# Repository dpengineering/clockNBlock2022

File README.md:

# ToDo List
[Google Doc Link](https://docs.google.com/document/d/1s_93HzQu_74fJWDLWwISt_NYs3OvQ41pf5nRqQ8sUA4/edit?usp=sharing).  
Please request access if you would like to change the doc or check things off.  

# ClockNBlock 2022 Version
Written by `@ArnavVWadhwa` and `@bvesper15` this is the new version of the clockNBlock project with the "shiny new delta arm." The major changes this year was to the circuit boards used. We added `@Stan-Reifel's` new DPi Circuit boards and redid the wiring. 
  
The code is also completely brand new and this is the third version of the code I have written. I hope it holds up to a good standard.

For any questions with the project feel free to reach out me.  
Arnav Wadhwa:  
(805) 570-5030.   
arnav.v.wadhwa@gmail.com

Note: When you contact me please let me know who you are and that this is for the clock and block so I don't accidently ignore you.

Here is the fun story for the project.
# It Clocks! It Blocks! New and improved only at Faker Maire!

# A Tale of Two Arms

This is the repository for the redesigned ClockNBlocks. The ClockNBlocks is a project in which a robotic arm stacks block towers, and sweeping clock hands susequently knock over the towers.

The project was first developed in the 2016-17 school year, employing a gantry-style serial manipulator arm. It wasn't fast; it wasn't elegant, but in ran like a beauty. The code for this version of the project was perfected by `@jproney` himself in the fall of 2017, and can be found here: https://github.com/dpengineering/ClockNBlockHW

After `@jproney's` labors to perfect the CNB, the original project was torn apart, and the slow, sturdy gantry arm replaced with a shiny new Delta Robot. What is a Delta Robot you ask? Luckily for you, `@jproney` made https://github.com/dpengineering/DeltaArm to answer this age old question. The DeltaArm repository contains the Inverse Kinematic and Forward Kinematic equations for controlling the new Delta Arm.

But that's not where the story ends. The original ClockNBlock was powered by an artificial brain known as the R-dwino (sometimes stylized _Arduino_). However, the new arm was to be controlled by a Pi of Raspberry and it's trusty companion, the Engine of Slush. Therefore, it became necessary for the Arduinos controlling the project's pneumatic actuators to communicate with the Rasperry Pi. To accomplish this task, `@jproney` created https://github.com/dpengineering/PythonManager by standing of the shoulders of `@jmgrosen`, the hero who first brought peace to Mechatronica. Unfortunately,
PythonManager was developed quite hastily, and is currently rather messy and confusing. 

And now that brings us here. The repository you are viewing combines the DeltaArm, PythonManager, and old ClockNBlockHW repositiories to create ClockNBlockPi. In its current state, the ClockNBlock runs, but not well. The arm control software (forward/inverse kinematics) works quite well, but for one reason or another the arm struggles to maintain the sub-inch precision required to pick up blocks consistently. This is likely due to backlash in the arm transmissions, slippage in shaft couplers, and inconsistencies in the homing of the arm.

Now you come into the story, young squire. Your task is to tame the Arm of Delta, build the Block Towers high once more, and bring the ClockNBlock back to its golden age. Godspeed.

Sincerely,
James "Petey/Stagflation/jproney" Roney

P.S. I did most (all) of these - Arnav

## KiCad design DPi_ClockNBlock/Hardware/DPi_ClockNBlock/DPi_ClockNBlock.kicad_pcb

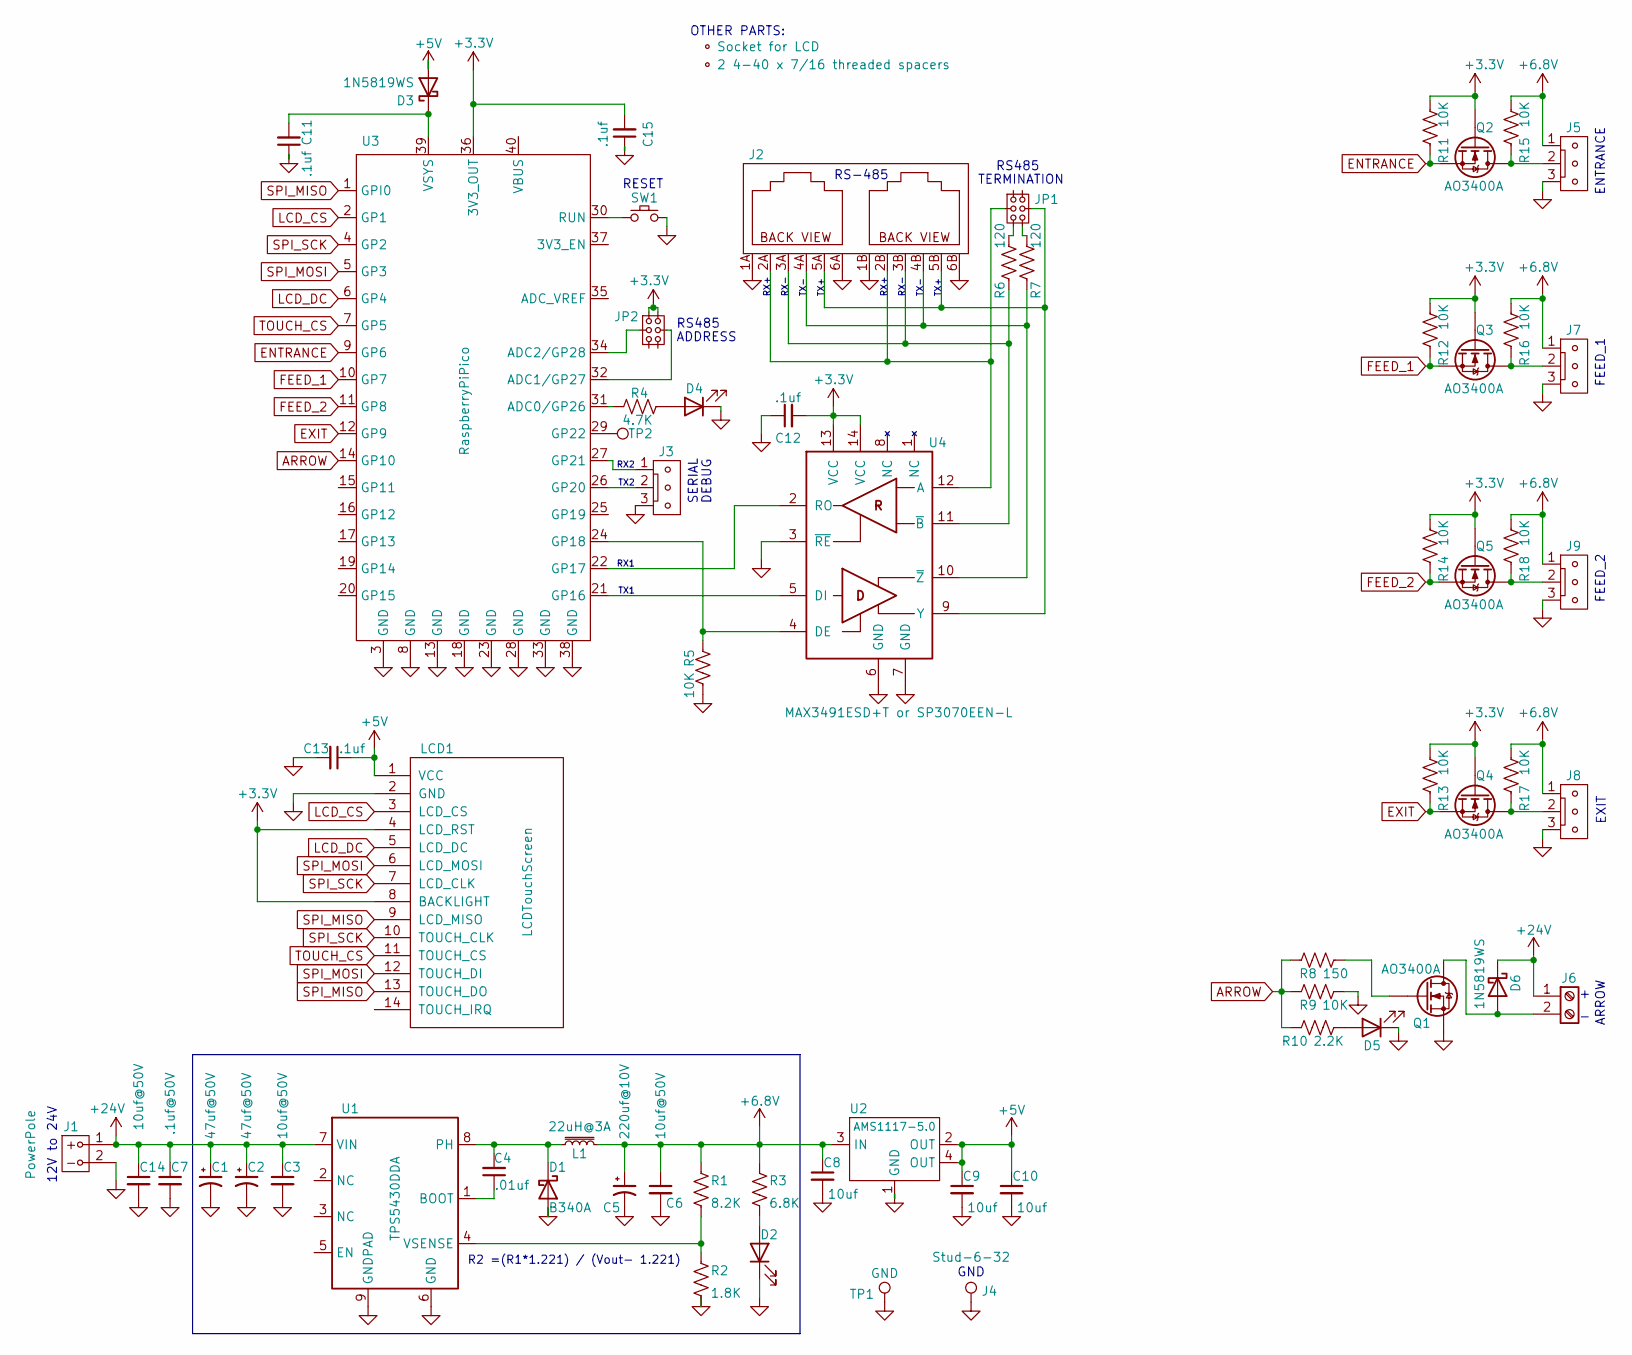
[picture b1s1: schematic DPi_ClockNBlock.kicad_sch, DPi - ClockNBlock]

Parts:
AP1: Socket for LCD
AP2: 2 4-40 x 7/16 threaded spacers
C1, C2: 47uf@50V; CP_Elec_6.3x7.7
C3, C6, C14: 10uf@50V; C_0805_2012Metric
C4: .01uf; C_0805_2012Metric
C5: 220uf@10V; CP_Elec_6.3x7.7
C7: .1uf@50V; C_0805_2012Metric
C8, C9, C10: 10uf; C_0805_2012Metric
C11, C12, C13, C15: .1uf; C_0805_2012Metric
D1: B340A; D_SMA
D2, D4, D5: RED LED; LED_0805_2012Metric
D3, D6: 1N5819WS; D_SOD-323
J1: PowerPole2
J2: 6P6C_Modular_Dual
J3, J5, J7, J8, J9: Molex-Vert-3-L; Molex-Vert-3
J4: Stud-6-32; ThreadedStud_6-32-375
J6: ScrewTerminal3.5MM-2
JP1, JP2: Jumper3x2
L1: 22uH@3A; Inductor_6.6x7.1_H3
LCD1: LCDTouchScreen
Q1, Q2, Q3, Q4, Q5: AO3400A; SOT-23
R1: 8.2K; R_0805_2012Metric
R2: 1.8K; R_0805_2012Metric
R3: 6.8K; R_0805_2012Metric
R4: 4.7K; R_0805_2012Metric
R5, R9, R11, R12, R13, R14, R15, R16, R17, R18: 10K; R_0805_2012Metric
R6, R7: 120; R_0805_2012Metric
R8: 150; R_0805_2012Metric
R10: 2.2K; R_0805_2012Metric
SW1: PushButton_C318884
TP1: GND; TestPoint
TP2: GP22; TestPoint
U1: TPS5430DDA; TI_SO-PowerPAD-8_ThermalVias
U2: AMS1117-5.0; SOT-223
U3: RaspberryPiPico
U4: MAX3491ESD+T or SP3070EEN-L; SOIC-14_3.9x8.7mm_P1.27mm

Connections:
+3V3: C12.2, C15.2, JP2.1, JP2.2, LCD1.4 (LCD_RST), LCD1.8 (BACKLIGHT), Q2.1 (G), Q3.1 (G), Q4.1 (G), Q5.1 (G), R11.2, R12.2, R13.2, R14.2, U3.36 (3V3_OUT), U4.13 (VCC), U4.14 (VCC)
+5V: C9.1, C10.1, C13.1, D3.2 (A), LCD1.1 (VCC), U2.2 (OUT), U2.4 (OUT)
+6.8V: C5.1, C6.1, C8.1, J5.1, J7.1, J8.1, J9.1, L1.2, R1.1, R3.1, R15.2, R16.2, R17.2, R18.2, U2.3 (IN)
+24V: C1.1, C2.1, C3.1, C7.1, C14.1, D6.1 (K), J1.1, J6.1, U1.7 (VIN)
ARROW: R8.1, R9.1, R10.1, U3.14 (GP10)
ENTRANCE: Q2.2 (S), R11.1, U3.9 (GP6)
EXIT: Q4.2 (S), R13.1, U3.12 (GP9)
FEED_1: Q3.2 (S), R12.1, U3.10 (GP7)
FEED_2: Q5.2 (S), R14.1, U3.11 (GP8)
GND: C1.2, C2.2, C3.2, C5.2, C6.2, C7.2, C8.2, C9.2, C10.2, C11.1, C12.1, C13.2, C14.2, C15.1, D1.2 (A), D2.1 (K), D4.1 (K), D5.1 (K), J1.2, J2.1A, J2.1B, J2.6A, J2.6B, J3.3, J4.1, J5.3, J7.3, J8.3, J9.3, LCD1.2 (GND), Q1.2 (S), R2.2, R5.2, R9.2, SW1.2, TP1.1, U1.6 (GND), U1.9 (GNDPAD), U2.1 (GND), U3.3 (GND), U3.8 (GND), U3.13 (GND), U3.18 (GND), U3.23 (GND), U3.28 (GND), U3.33 (GND), U3.38 (GND), U4.3 (~RE), U4.6 (GND), U4.7 (GND)
LCD_CS: LCD1.3 (LCD_CS), U3.2 (GP1)
LCD_DC: LCD1.5 (LCD_DC), U3.6 (GP4)
unnamed: C4.1, U1.1 (BOOT)
unnamed: C4.2, D1.1 (K), L1.1, U1.8 (PH)
unnamed: C11.2, D3.1 (K), U3.39 (VSYS)
unnamed: D2.2 (A), R3.2
unnamed: D4.2 (A), R4.2
unnamed: D5.2 (A), R10.2
unnamed: D6.2 (A), J6.2, Q1.3 (D)
unnamed: J2.2A, J2.2B, JP1.3, U4.12 (A)
unnamed: J2.3A, J2.3B, R6.1, U4.11 (~B)
unnamed: J2.4A, J2.4B, R7.1, U4.10 (~Z)
unnamed: J2.5A, J2.5B, JP1.4, U4.9 (Y)
unnamed: J3.1, U3.27 (GP21)
unnamed: J3.2, U3.26 (GP20)
unnamed: J5.2, Q2.3 (D), R15.1
unnamed: J7.2, Q3.3 (D), R16.1
unnamed: J8.2, Q4.3 (D), R17.1
unnamed: J9.2, Q5.3 (D), R18.1
unnamed: JP1.5, R6.2
unnamed: JP1.6, R7.2
unnamed: JP2.3, U3.34 (ADC2/GP28)
unnamed: JP2.4, U3.32 (ADC1/GP27)
unnamed: Q1.1 (G), R8.2
unnamed: R1.2, R2.1, U1.4 (VSENSE)
unnamed: R4.1, U3.31 (ADC0/GP26)
unnamed: R5.1, U3.24 (GP18), U4.4 (DE)
unnamed: SW1.1, U3.30 (RUN)
unnamed: TP2.1, U3.29 (GP22)
unnamed: U3.21 (GP16), U4.5 (DI)
unnamed: U3.22 (GP17), U4.2 (RO)
SPI_MISO: LCD1.9 (LCD_MISO), LCD1.13 (TOUCH_DO), U3.1 (GPI0)
SPI_MOSI: LCD1.6 (LCD_MOSI), LCD1.12 (TOUCH_DI), U3.5 (GP3)
SPI_SCK: LCD1.7 (LCD_CLK), LCD1.10 (TOUCH_CLK), U3.4 (GP2)
TOUCH_CS: LCD1.11 (TOUCH_CS), U3.7 (GP5)

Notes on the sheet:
SERIAL
TERMINATION
TX2
RX2
RX-
RESET
EXIT
TX+
RS-485
RX1
GND
ENTRANCE
12V to 24V
TX-
DEBUG
RS485
OTHER PARTS:
FEED_1
RX+
TX1
R2 =(R1*1.221) / (Vout- 1.221)
ADDRESS
ARROW
FEED_2

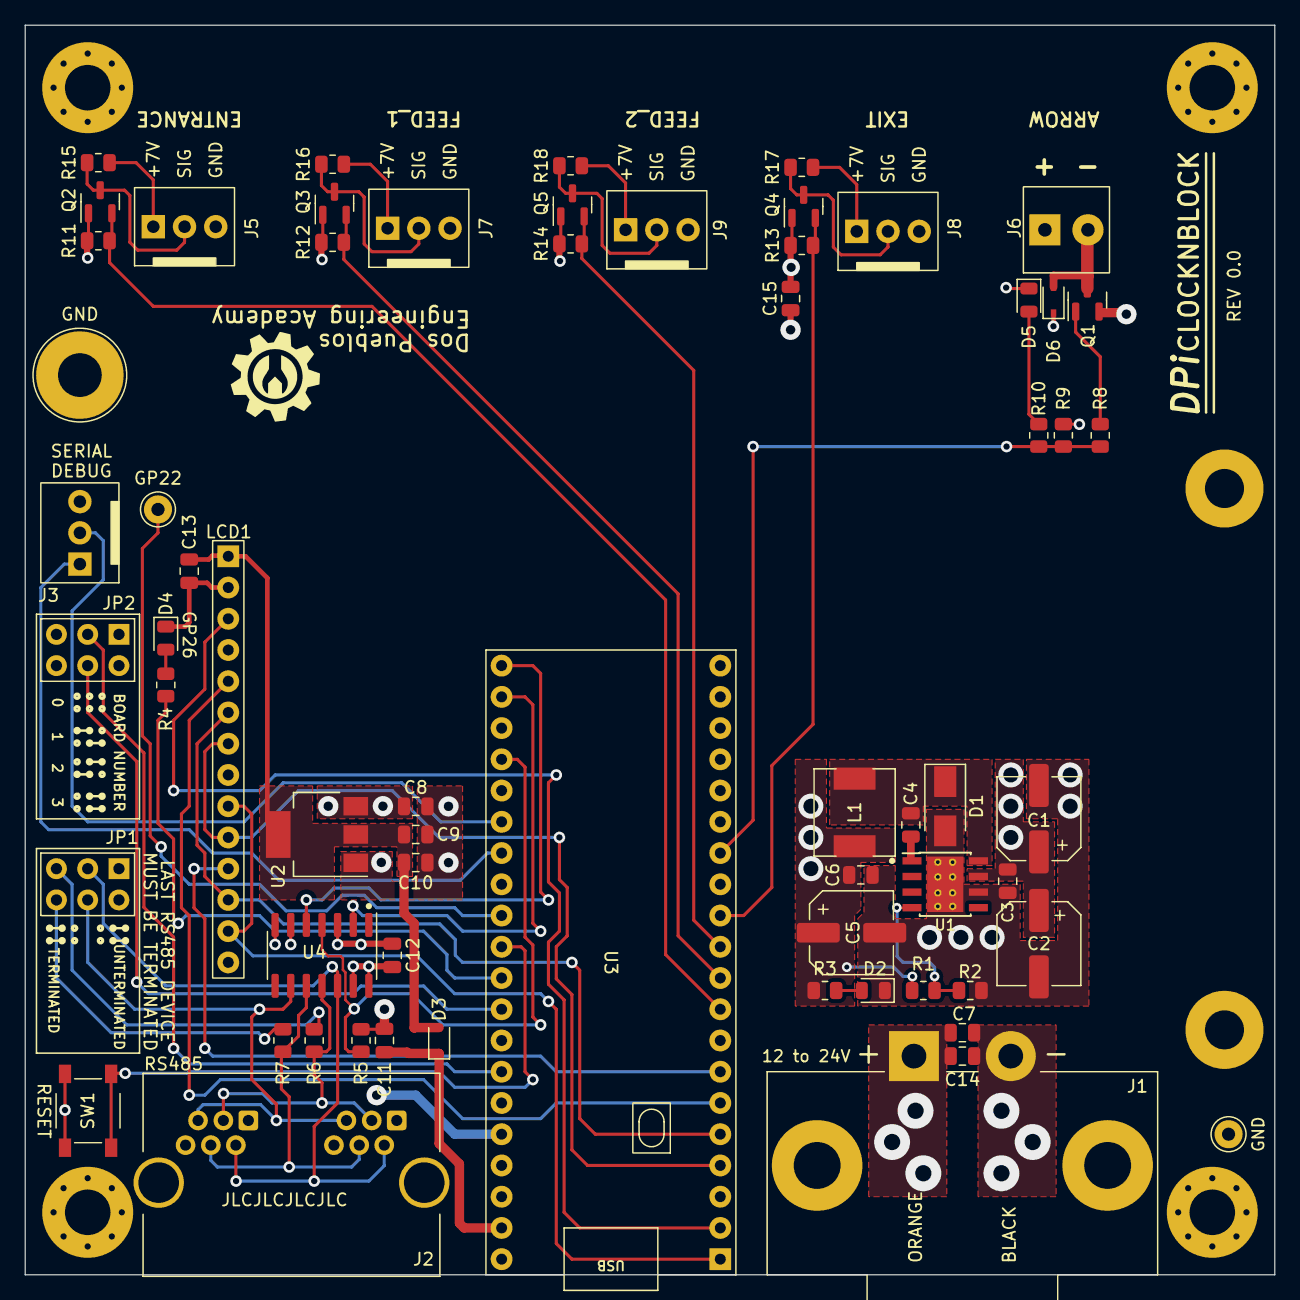
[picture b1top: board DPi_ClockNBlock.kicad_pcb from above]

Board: 4 copper layers, 101.6 x 101.6 mm, 64 parts (0 on the bottom side), 45 nets.

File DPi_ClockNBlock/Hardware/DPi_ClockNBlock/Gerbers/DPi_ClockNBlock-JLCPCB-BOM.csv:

Comment,Designator,Footprint,LCSC
47uf@50V,"C1,C2",Capacitor_SMD:CP_Elec_6.3x7.7,C401824
.1uf,"C11,C12,C13,C15",Capacitor_SMD:C_0805_2012Metric,C49678
10uf@50V,"C3,C6,C14",Capacitor_SMD:C_0805_2012Metric,C440198
.01uf,C4,Capacitor_SMD:C_0805_2012Metric,C1710
220uf@10V,C5,Capacitor_SMD:CP_Elec_6.3x7.7,C134763
.1uf@50V,C7,Capacitor_SMD:C_0805_2012Metric,C49678
10uf,"C8,C9,C10",Capacitor_SMD:C_0805_2012Metric,C440198
B340A,D1,Diode_SMD:D_SMA,C64982
RED LED,"D2,D4,D5",LED_SMD:LED_0805_2012Metric,C2297
1N5819WS,"D3,D6",Diode_SMD:D_SOD-323,C191023
22uH@3A,L1,@CustomFootprints_Discrete:Inductor_6.6x7.1_H3,C497873
AO3400A,"Q1,Q2,Q3,Q4,Q5",Package_TO_SOT_SMD:SOT-23,C20917
8.2K,R1,Resistor_SMD:R_0805_2012Metric,C17828
2.2K,R10,Resistor_SMD:R_0805_2012Metric,C17520
1.8K,R2,Resistor_SMD:R_0805_2012Metric,C17398
6.8K,R3,Resistor_SMD:R_0805_2012Metric,C17772
4.7K,R4,Resistor_SMD:R_0805_2012Metric,C17673
10K,"R5,R9,R11,R12,R13,R14,R15,R16,R17,R18",Resistor_SMD:R_0805_2012Metric,C17414
120,"R6,R7",Resistor_SMD:R_0805_2012Metric,C17437
150,R8,Resistor_SMD:R_0805_2012Metric,C17471
PushButton_C318884,SW1,@CustomFootprints_Discrete:PushButton_C318884,C318884
TPS5430DDA,U1,Package_SO:TI_SO-PowerPAD-8_ThermalVias,C9864
AMS1117-5.0,U2,Package_TO_SOT_SMD:SOT-223,C6187
MAX3491ESD+T or SP3070EEN-L,U4,Package_SO:SOIC-14_3.9x8.7mm_P1.27mm,C150204

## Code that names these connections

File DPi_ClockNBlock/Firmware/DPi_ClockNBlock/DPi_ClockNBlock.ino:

//      ******************************************************************
//      *                                                                *
//      *                       DPi - ClockNBlock                        *
//      *                                                                *
//      *            Arnav Wadhwa                  11/25/2022            *
//      *                                                                *
//      ******************************************************************

#include <Arduino.h>
#include "Constants.h"
#include "RS485Slave.h"
#include "CmdProcessor.h"

//
// variables global to this file
//
int boardNumber;


// ---------------------------------------------------------------------------------
//                              Hardware and software setup
// ---------------------------------------------------------------------------------

//
// top level setup function
//
void setup()
{
    debug_Initialize();
    debug("Starting...");

    //
    // initialize the all the inputs
    //
    pinMode(ENTRANCE_PIN, INPUT);
    pinMode(FEED_1_PIN, INPUT);
    pinMode(FEED_2_PIN, INPUT);
    pinMode(EXIT_PIN, INPUT);
 
    pinMode(ARROW_PIN, OUTPUT);
    digitalWrite(ARROW_PIN, LOW);

    //
    // determine the board number (as configured by jumps) for this board (0 - 3)
    //
    pinMode(RS486_ADDRESS_0_PIN, INPUT_PULLDOWN);
    pinMode(RS486_ADDRESS_1_PIN, INPUT_PULLDOWN);
    boardNumber = 0;
    if (digitalRead(RS486_ADDRESS_0_PIN)) boardNumber += 1;
    if (digitalRead(RS486_ADDRESS_1_PIN)) boardNumber += 2;

    //
    // initialize other IO lines
    //
    pinMode(LED_PIN, OUTPUT);
    digitalWrite(LED_PIN, LOW);
    pinMode(TEST_PIN, OUTPUT);

    //
    // initialize the software modules
    //
    cmdProcessor_Initialize(boardNumber);
    heartbeatLED_Initialize();
}


// ---------------------------------------------------------------------------------
//                      The Main Loop and Top Level Functions
// ---------------------------------------------------------------------------------


//
// main loop - execute commands from the Master
//
void loop()
{
    while(true)
    {
        //
        // check for and process commands from the Master
        //
        cmdProcessor_Execute();

        //
        // update the "heartbeat" LED
        //
        heartbeatLED_Update();
    }
}



// ---------------------------------------------------------------------------------
//                      Functions for the Heart Beat LED
// ---------------------------------------------------------------------------------

static int heartbeatState;
static int fastHeartbeatCount;
static unsigned long heartbeatStartTime;

//
// initialize the heart beat LED
//
void heartbeatLED_Initialize(void)
{
    heartbeatState = 0;
    fastHeartbeatCount = 0;
    heartbeatStartTime = millis();
}



//
// update the heartbeat
//
void heartbeatLED_Update(void)
{
    switch(heartbeatState)
    {
        case 0:
            if ((millis() - heartbeatStartTime) < 200) return;
            digitalWrite(LED_PIN, LOW);
            heartbeatStartTime = millis();
            heartbeatState = 1;
            return;
        case 1:
            if ((millis() - heartbeatStartTime) < 200) return;
            digitalWrite(LED_PIN, HIGH);
            heartbeatStartTime = millis();
            heartbeatState = 2;
            return;
        case 2:
            if ((millis() - heartbeatStartTime) < 200) return;
            digitalWrite(LED_PIN, LOW);
            heartbeatStartTime = millis();
            heartbeatState = 3;
            return;
        case 3:
            if ((millis() - heartbeatStartTime) < 430) return;
            digitalWrite(LED_PIN, HIGH);
            heartbeatStartTime = millis();
            heartbeatState = 0;
            return;

        case 10:
            if ((millis() - heartbeatStartTime) < 40) return;
            digitalWrite(LED_PIN, HIGH);
            heartbeatStartTime = millis();
            heartbeatState = 11;
            return;
        case 11:
            if ((millis() - heartbeatStartTime) < 40) return;
            digitalWrite(LED_PIN, LOW);
            heartbeatStartTime = millis();
            fastHeartbeatCount--;
            if (fastHeartbeatCount > 0)
                heartbeatState = 10;
            else
                heartbeatState = 3;
            return;
        default:
            heartbeatState = 0;
    }
}



//
// start the heart beating fast for a few cycles
//
void heartBeatLED_Fast(void)
{
    if (heartbeatState < 10)
        heartbeatState = 11;
    fastHeartbeatCount = 7;
}


// ---------------------------------------------------------------------------------
//                      Functions for debugging with serial
// ---------------------------------------------------------------------------------

//
// initialize debugging using print statements
//
void debug_Initialize(void)
{
    Serial2.setRX(DEBUG_RX_PIN);
    Serial2.setTX(DEBUG_TX_PIN);
    Serial2.begin(115200);
}



//
// debug using print statements
//
void debug(const char *s)
{
    Serial2.println(s);
}

void debug(const char *s, int i)
{
    Serial2.print(s);
    Serial2.print(": ");
    Serial2.println(i);
}

void debug(const char *s, float f)
{
    Serial2.print(s);
    Serial2.print(": ");
    Serial2.println(f);
}

// -------------------------------------- End --------------------------------------

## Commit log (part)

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2022-11-04 set up constants to initalize the linear delta arm
2022-11-07 Organized files and made a test for the robot arm
2022-11-07 Fixed typo in setup
2022-11-07 Added debugging prints
2022-11-07 It actually runs now
2022-11-07 removed unnessary checks
2022-11-07 typo
2022-11-07 example
2022-11-07 changed radius
2022-11-08 Wrote display block script
2022-11-08 fixed typo
2022-11-17 Started creating classes for each component
2022-11-28 Added DPiClockNBlock driver python file
2022-11-28 Fixed typo in gitignore file name
2022-11-29 Created very rough test for the DPi ClockNBlock firmware
2022-12-05 Started writing code for the clock
2022-12-05 Updated homing function in clockHands
2022-12-05 Fixed clock to go back to correct 12:00 position
2022-12-05 Fixed moveToTime string conversion
2022-12-06 Made the clock an object and added a few functions
2022-12-06 Fixed number of steps per rotation for hour hand
2022-12-06 Fixed error in moveToTimeRelative where dpiStepper.getCurrentPos returns a tuple
2022-12-08 Fixed clock alignment, changed initial setup to allow robot arm to move further down, added solenoid information
2022-12-08 Moved Stan's DPi_ClockNBlock directory to the correct git repo
2022-12-08 Fixed small issues and added the blockFeeder code
2022-12-08 Updated the DPiClockNBlock.py
2022-12-09 added easier training feature for robot arm
2022-12-09 changed input method to sys from pygame
2022-12-09 Fixed keystroke reader
2022-12-09 think everything is fixed but idk sometimes git just goes ham and idk why
2022-12-09 specified drivers for solenoids
2022-12-09 fixed solenoid driver numbers and changed movement for testing
2022-12-09 print
2022-12-09 moved print statement
2022-12-09 print stuff
2022-12-12 Wrote state function for the blockFeeders and fixed up the train robot function
2022-12-12 forgot to include the trainRobot file
2022-12-12 TrainRobot move isnt working, hopefully this fixes that
2022-12-12 For some reason it works now?
2022-12-12 this somehow fixed the training
2022-12-12 change writing to appending
2022-12-12 appending
2022-12-12 Added locations file
2022-12-13 Set 12:00 to the +y direction and the ready state for the block feeders is displaying a block
2022-12-13 fixed blockFeeder state function
2022-12-13 fixed training function
2022-12-13 fixed change stepSize
2022-12-13 added state function for arm
2022-12-13 Started on block manager
2022-12-13 added build state
2022-12-13 added some comments
2022-12-13 added actionAvailable()
2022-12-14 Did some reorganizing and started on blockManager
2022-12-15 Worked on logic to move robot arm
2022-12-15 First draft of robot arm logic
2022-12-16 moving computers
2022-12-16 fixed errors in the ClockNBlock Library
2022-12-16 Fixed max clock speed and debugging blockFeeders
2022-12-27 Resturctured files and updated state functions for robot arm
2023-01-03 Fixing bugs
2023-01-03 varius small changes
2023-01-04 debugging
2023-01-04 adding prints
2023-01-04 fixed block manager clock stuff
2023-01-04 fixed typos and poor copy pasting
2023-01-05 pemdas :(
2023-01-05 Added comments and documentation for code
2023-01-05 Finished debugging
2023-01-05 Reverting clockHands.py back to a previous version
2023-01-05 Fixed multiplier for clockSpeed
2023-01-05 Figuring out limits
2023-01-05 adjusting parameters
2023-01-06 Added ensureStraightLine so the robot always moves in a straight line instead of a curve
2023-01-06 Changing ensure line
2023-01-06 updating
2023-01-09 First draft of making the hour hand a pointer
2023-01-09 Checking if ensureStraightLine() works (It does)
2023-01-09 debugging small errors
2023-01-11 Debugging jerky robot arm mobe
2023-01-12 debugging stuff
2023-01-13 commented run.py
2023-01-17 changing parameters
2023-01-17 Testing block Feeders
2023-01-20 final adjusting of parameters
2023-01-24 New straight line method
2023-01-24 changing some parameters
2023-01-25 Added blink arrow function to firmware and implemented it in the blockfeeder object
2023-01-25 debigging
2023-01-26 Finishing up with all of the code
2023-01-30 Made minute hand stop when robot idle
2023-01-31 Made a general way to move the robot with a joystick
2023-01-31 Fixed a few oversights in training script
2023-01-31 Updated joystick control
2023-02-01 Fixed minor bug
2023-02-06 Training robot using joystick added
2023-02-06 adding some joystick functionality
2023-02-06 training
2023-02-13 Added robot e-stop handler
2023-02-24 training new locations
2023-02-24 done training
2023-02-24 updated trained locations
2023-02-24 hands.setup() returns True
2023-02-24 debugging run.py
2023-02-24 debugging robot arm
2023-02-24 disabled arrow
2023-02-24 testFeederProgram
2023-02-27 editing debug messages and simplifying code a little bit
2023-02-27 list comphrension didnt work
2023-02-28 creating multiple tower configurations
2023-02-28 changed rotation timing
2023-02-28 adjusted build locations
2023-02-28 changed block placement list from array
2023-02-28 final version after adjusting
2023-03-02 optimizing Z travel height
2023-03-02 Adjusting hand speed
2023-03-02 fixed minimum moving height
2023-03-03 Start of 5 day counter #1
2023-03-08 done debugging
2023-03-08 debugging some movement errors that is causing robot to lose steps
2023-03-09 lowered speeds
2023-03-17 adjusting final parameters
2023-04-03 started on documentation
2023-04-03 pseudo merge with code on the DPEA computers
2023-04-03 adding little pointers to see where the setup hangs
2023-04-03 debug
2023-04-05 Refactoring code and starting to give personality to the robot arm
2023-04-05 working on fleshing out the clock. More to be done
2023-04-05 testing Clock functions
2023-04-05 Adding methods to robotArm. Need to change locations from radians to degrees
2023-04-05 dialing in the steps per revolution for the hands
2023-04-05 Ready to Train New Points
2023-04-06 Fixed cartesianToPolar and added a small robot arm test
2023-04-06 added adjustment for step size in robot training
2023-04-06 restructuring files and placing objects where they make more sense
2023-04-06 update gitignore
2023-04-06 updated button placements
2023-04-06 trained locations
2023-04-06 adjusted training locations
2023-04-06 added locations, placement arrays. Working on BuildSites now
2023-04-07 Feeders, clock need testing, robot arm, manager need to be finished
2023-04-07 debugged block feeders
2023-04-10 plane code, still working on robot manager
2023-04-10 removed intersectionPolygon from BuildSite as Sympy does not support 3D polygons. Will map the intersection polygon onto the created plane
2023-04-10 first working draft of robotManager.checkIntersectionCartesian()
2023-04-11 Polar moves and cartesian moves done - untested.
2023-04-12 dodging obstacle and planning zig-zag moves
2023-04-13 Testing Version 1. Does not have personality right now
2023-04-13 Debugging this version
2023-04-13 Fixed circular imports
2023-04-13 Fixing import statements
2023-04-13 Fixed setup procedure
2023-04-13 Debugging import statements and clock.process()
2023-04-13 Debugging import statements and robotarm.process()
2023-04-13 Debugging and adding print statements. Debugging RobotManager and adding print statements to clock and main
2023-04-13 Debugging robotManager.
2023-04-13 setting up buildSties
2023-04-13 debugging robotManager.py
2023-04-13 debugging robotManager.py and blockFeeder.py
2023-04-13 Removing print statement. Debug with the actual debugger now...
2023-04-14 Debugging and rewriting ensureStraightLineCartesian()
2023-04-14 debugging with debugger
2023-04-14 Fixing bugs in robotManager.py
2023-04-17 Bugfix for generatePlacementList() and beginning on planZigZagMove()
2023-04-18 cleaning up code
2023-04-18 debugging branch created
2023-04-18 debugging crashes
2023-04-19 testing version for regular movement, expecting a lot of bugs
2023-04-19 Forgot to change clock to being a pointer
2023-04-19 adding offset, not sure if this is needed, good to try
2023-04-19 fixing clock bugs, fix ensureStraightLine now
2023-04-19 docs for debugging
2023-04-20 working on docs
2023-04-20 debugged ensureStraightLine, error was in polarToCartesian
2023-04-20 debugging and updating gitignore
2023-04-20 debugging, work on feeders ready flag next
2023-04-21 Fixing false ready states for blockFeeder and blockManager, adding docs and testing
2023-04-21 documentation to configure the robot board
2023-04-21 debugged
2023-04-21 stopping clock when robot is idle
2023-04-21 final debug
2023-04-21 Commented print statements for debugging
2023-04-23 Updating Imbuing Personality, also wrote ZigZag method. Needs debugging
2023-04-23 First debugging round of planZigZag, Starting Spiral next
2023-04-23 Added Spiral Move, will need debugging
2023-04-23 Making code prettier
2023-04-24 Writing final methods and tests
2023-04-24 Renamed Documentation folder
2023-04-24 Updated testClockMovement.py
2023-04-24 Adding to docs
2023-04-24 debugged, need to fix ZigZag and hour hand
2023-04-25 Changed spiral move to circle, updated zigZag, added tests. TODO: Debug ZigZag
2023-04-25 Updated getPositionDegrees() in clock.py
2023-04-25 debugging testZigZag.py. Probably will have to rewrite the whole thing
2023-04-26 rewrote planZigZag(). Hopefully works now. Needs testing
2023-04-26 Updating zigzag to debug a small amount
2023-04-26 Debugged zigZag move, might need a check to avoid running into the posts
2023-04-26 circles are circular
2023-04-26 fixing polar moves
2023-04-26 updated plan polar move
2023-04-26 idk ask arnav
2023-04-27 Added a small buffer in fakePlacement. Previous commit fixed rotation for getting a block from another tower
2023-04-27 A very small update to docs. More to come
2023-04-27 Updating zigZag to not hit poles
2023-04-27 clock and robot need debugging
2023-05-01 removed dodging obstacles, added back fake placement
2023-05-01 added test dpiStepper
2023-05-01 Removed FakePlacement and stopped blinking arrow in blockfeeder setup
2023-05-02 Locations for exclusion Zones
2023-05-02 Updated planning moves, changed clock movement
2023-05-02 removed fake placement
2023-05-02 Every 5 minutes, home robot
2023-05-03 Updated Docs and created startup script
2023-05-03 Updated methods and docs
2023-05-03 removing __pycache__ folders
2023-05-03 removed more __pycache__ folders
2023-05-04 Updated avoiding poles and planning polar moves. There is a merge necessary on computer in DPEA. Forgot to push
2023-05-04 Updated homing every 5 minutes
2023-05-04 Robot Arm homing state
2023-05-04 Fixed HourHandPosition for pointing
2023-05-05 Editing movement planning
2023-06-01 Changed build height of small tower to be one block shorter for showcase
